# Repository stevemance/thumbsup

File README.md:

# ThumbsUp - Antweight Combat Robot Control System

A complete control system for a 1lb (454g) combat robot using Raspberry Pi Pico W and Bluetooth gamepad control.

## Features

- **Bluetooth Control**: Universal gamepad support via Bluepad32 library (Xbox, PlayStation, Switch Pro, etc.)
- **Differential Drive**: Tank-style mixing with exponential curves for smooth control
- **Weapon Control**: Variable speed brushless weapon with safety arming sequence
- **Safety Systems**: Multiple failsafes including connection loss detection and battery monitoring
- **Status Indicators**: LED feedback for system state, weapon armed, and battery status

## Hardware Components

### Core Electronics
- **Microcontroller**: Raspberry Pi Pico W
- **Power**: 3S LiPo battery (11.1V nominal)

### Motor System
- **Drive Motors**: Repeat Mini Brushed Mk2 (3mm shaft)
- **Drive ESC**: 2-channel brushed motor controller
- **Weapon Motor**: F2822-1100KV brushless outrunner
- **Weapon ESC**: AM32 40A 32-bit ESC

### Control
- **Controller**: Any Bluetooth gamepad supported by Bluepad32
- **Protocol**: Bluetooth Classic (BR/EDR) and BLE support
- **Supported Controllers**: Xbox One/Series, PlayStation 3/4/5, Switch Pro, 8BitDo, and more

## Pin Configuration

| Pin | Function | Description |
|-----|----------|-------------|
| GP0 | PWM Output | Left drive motor signal |
| GP1 | PWM Output | Right drive motor signal |
| GP4 | PWM/DShot Output | Weapon motor signal |
| GP8 | GPIO Input | Safety button (optional, pull-up) |
| GP26 | ADC Input | Battery voltage monitor (ADC0) |
| GP28 | Data Output | SK6812 status LEDs |
| VSYS | Power In | 5V from ESC BEC |
| GND | Ground | Common ground |

See `docs/HARDWARE_SETUP.md` for the full wiring guide.

## Documentation

### 📖 User Manuals
- **[User Manual](docs/USER_MANUAL.md)** - Complete operating instructions, safety procedures, and troubleshooting
- **[Quick Reference](docs/QUICK_REFERENCE.md)** - Single-page quick reference for competition use
- **[Hardware Setup](docs/HARDWARE_SETUP.md)** - Complete pin configuration and wiring guide
- **[HITL (Hardware In The Loop)](docs/HITL.md)** - Fully automated end-to-end tests (robot + emulated controller + host orchestrator)
- **[Building Guide](docs/building.md)** - Compilation and setup instructions
- **[Wiring Guide](docs/wiring_guide.md)** - Hardware connection diagrams

### Control Mapping Summary

| Control | Function |
|---------|----------|
| Left Stick | Drive control (forward/back + turning) |
| Right Stick Y | Weapon speed control (when armed) |
| B Button | Arm/disarm weapon toggle |
| A Button (hold 2s) | Clear emergency stop |
| L1 + R1 | Emergency stop (all motors) |

## Safety Features

### Startup Safety Tests
The robot performs 6 critical safety tests on every startup:

1. **Motor Initialization** - Verifies all motors start in safe positions
2. **Weapon Safety** - Confirms weapon starts disarmed and interlocks work
3. **Failsafe System** - Tests signal loss detection (1.5 second timeout)
4. **Battery Monitoring** - Validates voltage sensing and thresholds
5. **Emergency Stop** - Verifies E-stop functionality
6. **Overflow Protection** - Ensures calculation safety

If any test fails, the robot enters lockout mode with rapid LED flashing and will not operate.

### Runtime Safety Features
- **Connection failsafe** - Motors stop after 1.5s signal loss
- **Low battery protection** - Weapon disabled below 11.1V
- **Emergency stop** - L1+R1 instantly stops all motors
- **Continuous monitoring** - Safety checks run every 10ms
- **Violation counting** - Multiple violations trigger automatic shutdown

## Building the Firmware

### Prerequisites

1. Install the Raspberry Pi Pico SDK:
```bash
git clone https://github.com/raspberrypi/pico-sdk.git
cd pico-sdk
git submodule update --init
export PICO_SDK_PATH=$PWD
```

2. Install Bluepad32:
```bash
git clone https://github.com/ricardoquesada/bluepad32.git
cd bluepad32
git submodule update --init
export BLUEPAD32_ROOT=$PWD
```

3. Install required tools:
```bash
sudo apt update
sudo apt install cmake gcc-arm-none-eabi build-essential
# Install picotool for UF2 generation
cd ~/
git clone https://github.com/raspberrypi/picotool.git
cd picotool
mkdir build && cd build
cmake .. && make
sudo make install
```

### Build Process

#### Quick Build
```bash
export PICO_SDK_PATH=/path/to/pico-sdk
export BLUEPAD32_ROOT=/path/to/bluepad32
cd thumbsup/firmware
mkdir build && cd build
cmake ..
make -j8
```

Output: `firmware/build/thumbsup.uf2`

## Flashing the Firmware

1. Hold the BOOTSEL button on the Pico W
2. Connect the Pico W to your computer via USB
3. Release the BOOTSEL button
4. The Pico will appear as a USB drive
5. Copy `thumbsup.uf2` to the drive
6. The Pico will automatically reboot with the new firmware

## AM32 ESC Configuration

The weapon ESC needs specific configuration for optimal performance:

- Canonical expected AM32 EEPROM config for HITL is tracked at `config/am32/weapon_esc_expected.hexcfg`.
- HITL orchestrator checks/applies this config automatically (write-on-drift) unless `--no-am32-provision` is used.

### Using AM32 Configurator

1. Download AM32 Configurator from [GitHub](https://github.com/AlkaMotors/AM32-MultiRotor-ESC-firmware)
2. Connect the ESC to your computer using a USB-serial adapter
3. Apply these settings:

```
Motor Direction: Forward
Brake on Stop: OFF
Motor Timing: 16 degrees
Startup Power: Medium
PWM Frequency: 24kHz
Temperature Protection: 80°C
Low Voltage Cutoff: Disabled (managed by robot firmware)
Throttle Calibration: 1000-2000μs
Signal Type: Normal PWM
```

## Safety Procedures

### Pre-Competition Checklist

1. **Battery Check**: Ensure battery voltage > 10V
2. **Connection Test**: Verify gamepad connects automatically
3. **Failsafe Test**: Turn off controller, verify motors stop
4. **Weapon Arm**: Test arm sequence (X+Y hold)
5. **Emergency Stop**: Test L1+R1 disarm

### Operating Procedures

1. Power on robot with weapon ESC disconnected
2. Verify drive functions correctly
3. Connect weapon ESC
4. Arm weapon only when in combat arena
5. Always disarm before handling robot

## Wiring Diagram

### Power Distribution
```
3S LiPo Battery
    |
    +-- Drive ESC Power
    |     |
    |     +-- 5V BEC --> Pico VSYS
    |
    +-- Weapon ESC Power
          |
          +-- 1000μF Capacitor (parallel)
```

### Signal Connections
```
Pico GP2 --> Drive ESC CH1 Signal
Pico GP3 --> Drive ESC CH2 Signal
Pico GP4 --> Weapon ESC Signal
All ESC Grounds --> Pico GND
```

### Battery Monitor
```
Battery + --[10kΩ]--+--[3.3kΩ]-- GND
                    |
                 Pico GP26
```

## Troubleshooting

### Bluetooth Connection Issues
- Ensure controller is in pairing mode (varies by controller type)
- Check STATUS LED for connection state
- Reset Pico if connection fails after 10 seconds
- Bluepad32 automatically handles pairing for supported controllers
- For first-time pairing, controller may need to be in discovery mode

### Motor Not Responding
- Verify PWM signal with oscilloscope/logic analyzer
- Check ESC power and ground connections
- Ensure ESC is calibrated for 1000-2000μs range

### Weapon Won't Arm
- Check battery voltage (must be > 9.6V)
- Verify arm sequence is held for full duration
- Check ARMED LED for feedback

## Development

### Debug Mode

Debug output is enabled by default. Connect via serial terminal (115200 baud) to see:
- Bluepad32 controller detection and pairing status
- Gamepad input values
- System state changes

To disable debug output, remove `DEBUG_MODE=1` from the source files.

### Modifying Parameters

Edit `firmware/include/config.h` to adjust:
- Control deadzones
- Speed limits
- Exponential curves
- Timing constants
- Safety thresholds

### Bluetooth Platform Customization

The Bluepad32 platform implementation is in `firmware/src/bluetooth_platform.c`.
Modify the callbacks to customize:
- Controller mapping
- Input processing
- Special button combinations
- Rumble/LED feedback

## CAD Files

Mechanical design files are hosted on Onshape:
[Link to be provided]

## License

This project is open source hardware and software.
- Software: MIT License
- Hardware: CERN-OHL-S v2

## Safety Warning

This is a combat robot with dangerous spinning weapons. Always:
- Wear safety glasses when operating
- Keep weapon pointed away from people
- Use proper arena/test box
- Follow event safety rules
- Have emergency stop ready

## Support

For issues or questions, please open an issue on GitHub.

---

Built with safety and performance in mind for antweight combat robotics.

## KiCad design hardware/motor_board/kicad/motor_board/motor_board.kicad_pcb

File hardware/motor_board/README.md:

# ThumbsUp motor board

Battery in, three brushless channels out, 5 V to the compute board.  Sensorless weapon
(DRV8323RH + 6 FETs), two FOC drive motors with Hall/encoder feedback (2 × DRV8316C), one
STM32G474 running all three, 4S.  Battery input, reverse-polarity protection, pack
monitoring (INA239: V, I, P; BQ76907: per-cell voltages), a soft-start power switch and all
regulation live here.  195 JLC-assembled parts (rev L, after thirty adversarial review rounds in
[review/](review/), then a trim of the speculative firmware policy they had accumulated).

Start with [DESIGN.md](DESIGN.md).  Draw the schematic from [design/nets.md](design/nets.md)
(generated from [design/motor_board.py](design/motor_board.py)); parts in [BOM.md](BOM.md);
MCU pins in [design/mcu_pinmap.md](design/mcu_pinmap.md); SPICE checks in [spice/](spice/);
datasheets in [datasheets/](datasheets/).

```
python3 design/motor_board.py      # re-check the netlist and regenerate nets/BOM/pinmap
python3 design/calcs.py            # regenerate the sizing tables
../tools/.venv/bin/python spice/sim_hotplug.py   # etc., see spice/README.md
```

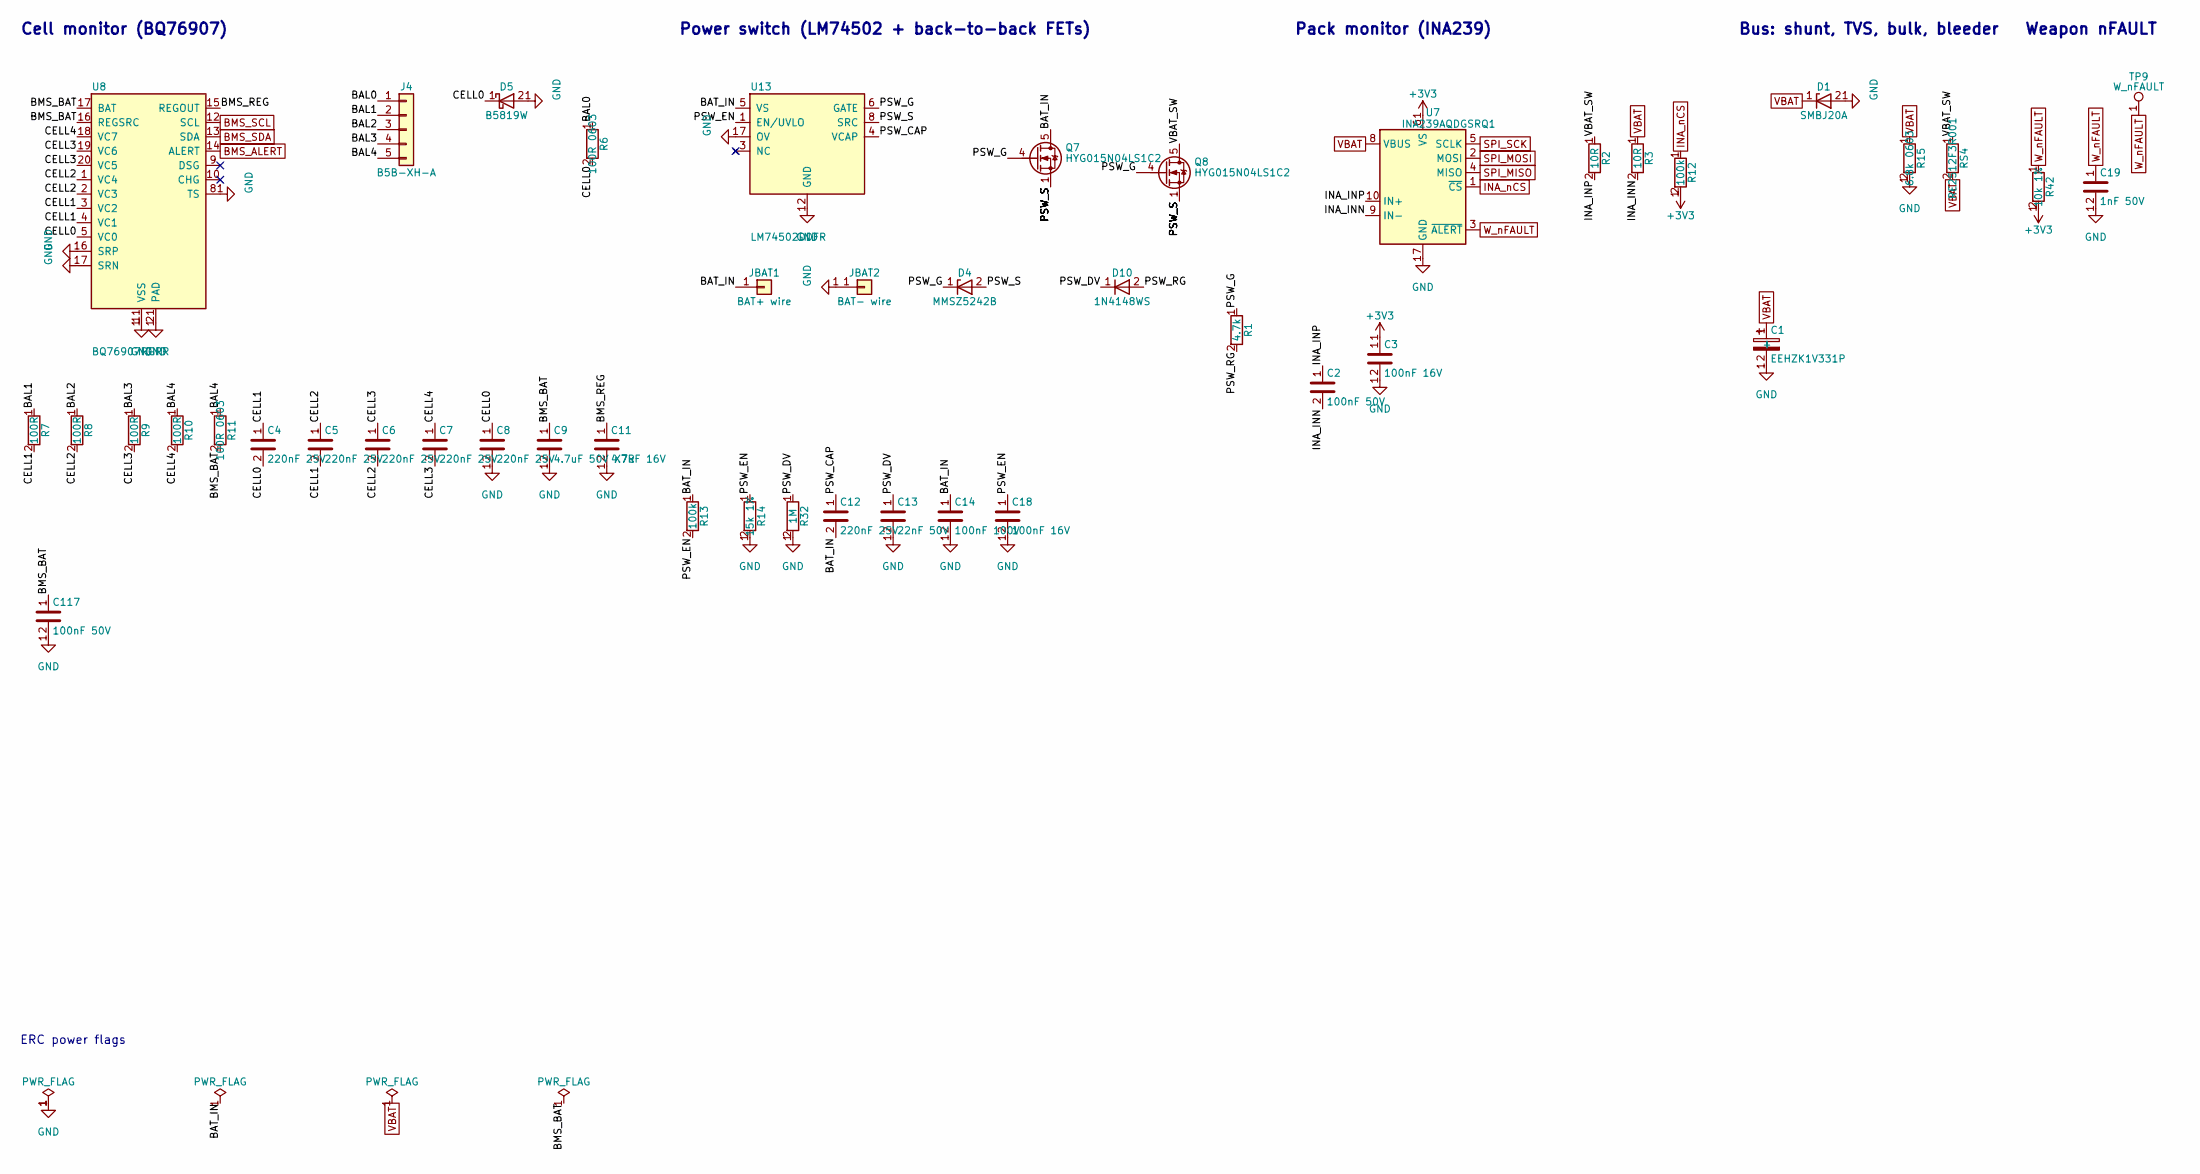
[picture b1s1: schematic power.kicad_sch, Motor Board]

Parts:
C1: EEHZK1V331P; CP_Elec_10x10.5; MPN EEHZK1V331P; LCSC C278516
C2, C117: 100nF 50V; C_0603_1608Metric; LCSC C14663
C3, C18: 100nF 16V; C_0402_1005Metric; LCSC C1525
C4, C5, C6, C7, C8, C12: 220nF 25V; C_0603_1608Metric; LCSC C21120
C9: 4.7uF 50V X7R; C_1206_3216Metric; LCSC C29823
C11: 4.7uF 16V; C_0603_1608Metric; LCSC C19666
C13: 22nF 50V; C_0603_1608Metric; LCSC C21122
C14: 100nF 100V; C_0603_1608Metric; LCSC C15725
C19: 1nF 50V; C_0402_1005Metric; LCSC C1523
D1: SMBJ20A; D_SMB; MPN SMBJ20A; LCSC C151922
D4: MMSZ5242B; D_SOD-123; MPN MMSZ5242B; LCSC C21567
D5: B5819W; D_SOD-123; MPN B5819W; LCSC C8598
D10: 1N4148WS; D_SOD-323; MPN 1N4148WS; LCSC C2128
J4: B5B-XH-A; JST_XH_B5B-XH-A_1x05_P2.50mm_Vertical; MPN B5B-XH-A; LCSC C157991
JBAT1: BAT+ wire; SolderWire-1.5sqmm_1x01_D1.7mm_OD3.9mm
JBAT2: BAT- wire; SolderWire-1.5sqmm_1x01_D1.7mm_OD3.9mm
Q7, Q8: HYG015N04LS1C2; PQFN-8-EP_6x5mm_P1.27mm_Generic; MPN HYG015N04LS1C2; LCSC C2874970
R1: 4.7k; R_0402_1005Metric; LCSC C25900
R2, R3: 10R; R_0402_1005Metric; LCSC C25077
R6, R11: 100R 0603; R_0603_1608Metric; LCSC C22775
R7, R8, R9, R10: 100R; R_0402_1005Metric; LCSC C25076
R12, R13: 100k; R_0402_1005Metric; LCSC C25741
R14: 15k 1%; R_0402_1005Metric; LCSC C25756
R15: 6.8k 0603; R_0603_1608Metric; LCSC C23212
R32: 1M; R_0402_1005Metric; LCSC C26083
R42: 10k 1%; R_0402_1005Metric; LCSC C25744
RS4: RE2512F3R001; R_2512_JIERR_RE_small_electrode; MPN RE2512F3R001; LCSC C46961745
TP9: W_nFAULT; TestPoint_Pad_D1.0mm
U7: INA239AQDGSRQ1; MSOP-10_3x3mm_P0.5mm; MPN INA239AQDGSRQ1; LCSC C4367136
U8: BQ76907RGRR; QFN-20-1EP_3.5x3.5mm_P0.5mm_EP2x2mm; MPN BQ76907RGRR; LCSC C22458649
U13: LM74502DDFR; Texas_DDF0008A_SOT-8_1.6x2.9mm_P0.65mm; MPN LM74502DDFR; LCSC C3236215

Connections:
+3V3: C3.1, R12.2, R42.2, U7.6 (VS); also elsewhere on the board
/power/BAL0: J4.1, R6.1
/power/BAL1: J4.2, R7.1
/power/BAL2: J4.3, R8.1
/power/BAL3: J4.4, R9.1
/power/BAL4: J4.5, R10.1, R11.1
/power/BAT_IN: C12.2, C14.1, JBAT1.1, Q7.5 (D), R13.1, U13.5 (VS)
/power/BMS_BAT: C9.1, C117.1, R11.2, U8.16 (REGSRC), U8.17 (BAT)
/power/BMS_REG: C11.1, U8.15 (REGOUT)
/power/CELL0: C4.2, C8.1, D5.1 (K), R6.2, U8.5 (VC0)
/power/CELL1: C4.1, C5.2, R7.2, U8.3 (VC2), U8.4 (VC1)
/power/CELL2: C5.1, C6.2, R8.2, U8.1 (VC4), U8.2 (VC3)
/power/CELL3: C6.1, C7.2, R9.2, U8.19 (VC6), U8.20 (VC5)
/power/CELL4: C7.1, R10.2, U8.18 (VC7)
/power/INA_INN: C2.2, R3.2, U7.9 (IN-)
/power/INA_INP: C2.1, R2.2, U7.10 (IN+)
/power/PSW_CAP: C12.1, U13.4 (VCAP)
/power/PSW_DV: C13.1, D10.1 (K), R32.1
/power/PSW_EN: C18.1, R13.2, R14.1, U13.1 (EN/UVLO)
/power/PSW_G: D4.1 (K), Q7.4 (G), Q8.4 (G), R1.1, U13.6 (GATE)
/power/PSW_RG: D10.2 (A), R1.2
/power/PSW_S: D4.2 (A), Q7.1 (S), Q7.2 (S), Q7.3 (S), Q8.1 (S), Q8.2 (S), Q8.3 (S), U13.8 (SRC)
/power/VBAT_SW: Q8.5 (D), R2.1, RS4.1
BMS_ALERT: U8.14 (ALERT); also elsewhere on the board
BMS_SCL: U8.12 (SCL); also elsewhere on the board
BMS_SDA: U8.13 (SDA); also elsewhere on the board
GND: C1.2 (-), C3.2, C8.2, C9.2, C11.2, C13.2, C14.2, C18.2, C19.2, C117.2, D1.2 (A), D5.2 (A), JBAT2.1, R14.2, R15.2, R32.2, U7.7 (GND), U8.6 (SRP), U8.7 (SRN), U8.8 (TS), U8.11 (VSS), U8.21 (PAD), U13.2 (GND), U13.7 (OV); also elsewhere on the board
INA_nCS: R12.1, U7.1 (~CS); also elsewhere on the board
SPI_MISO: U7.4 (MISO); also elsewhere on the board
SPI_MOSI: U7.2 (MOSI); also elsewhere on the board
SPI_SCK: U7.5 (SCLK); also elsewhere on the board
VBAT: C1.1 (+), D1.1 (K), R3.1, R15.1, RS4.2, U7.8 (VBUS); also elsewhere on the board
W_nFAULT: C19.1, R42.1, TP9.1, U7.3 (~ALERT); also elsewhere on the board

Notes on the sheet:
ERC power flags
Cell monitor (BQ76907)
Power switch (LM74502 + back-to-back FETs)
Pack monitor (INA239)
Bus: shunt, TVS, bulk, bleeder
Weapon nFAULT

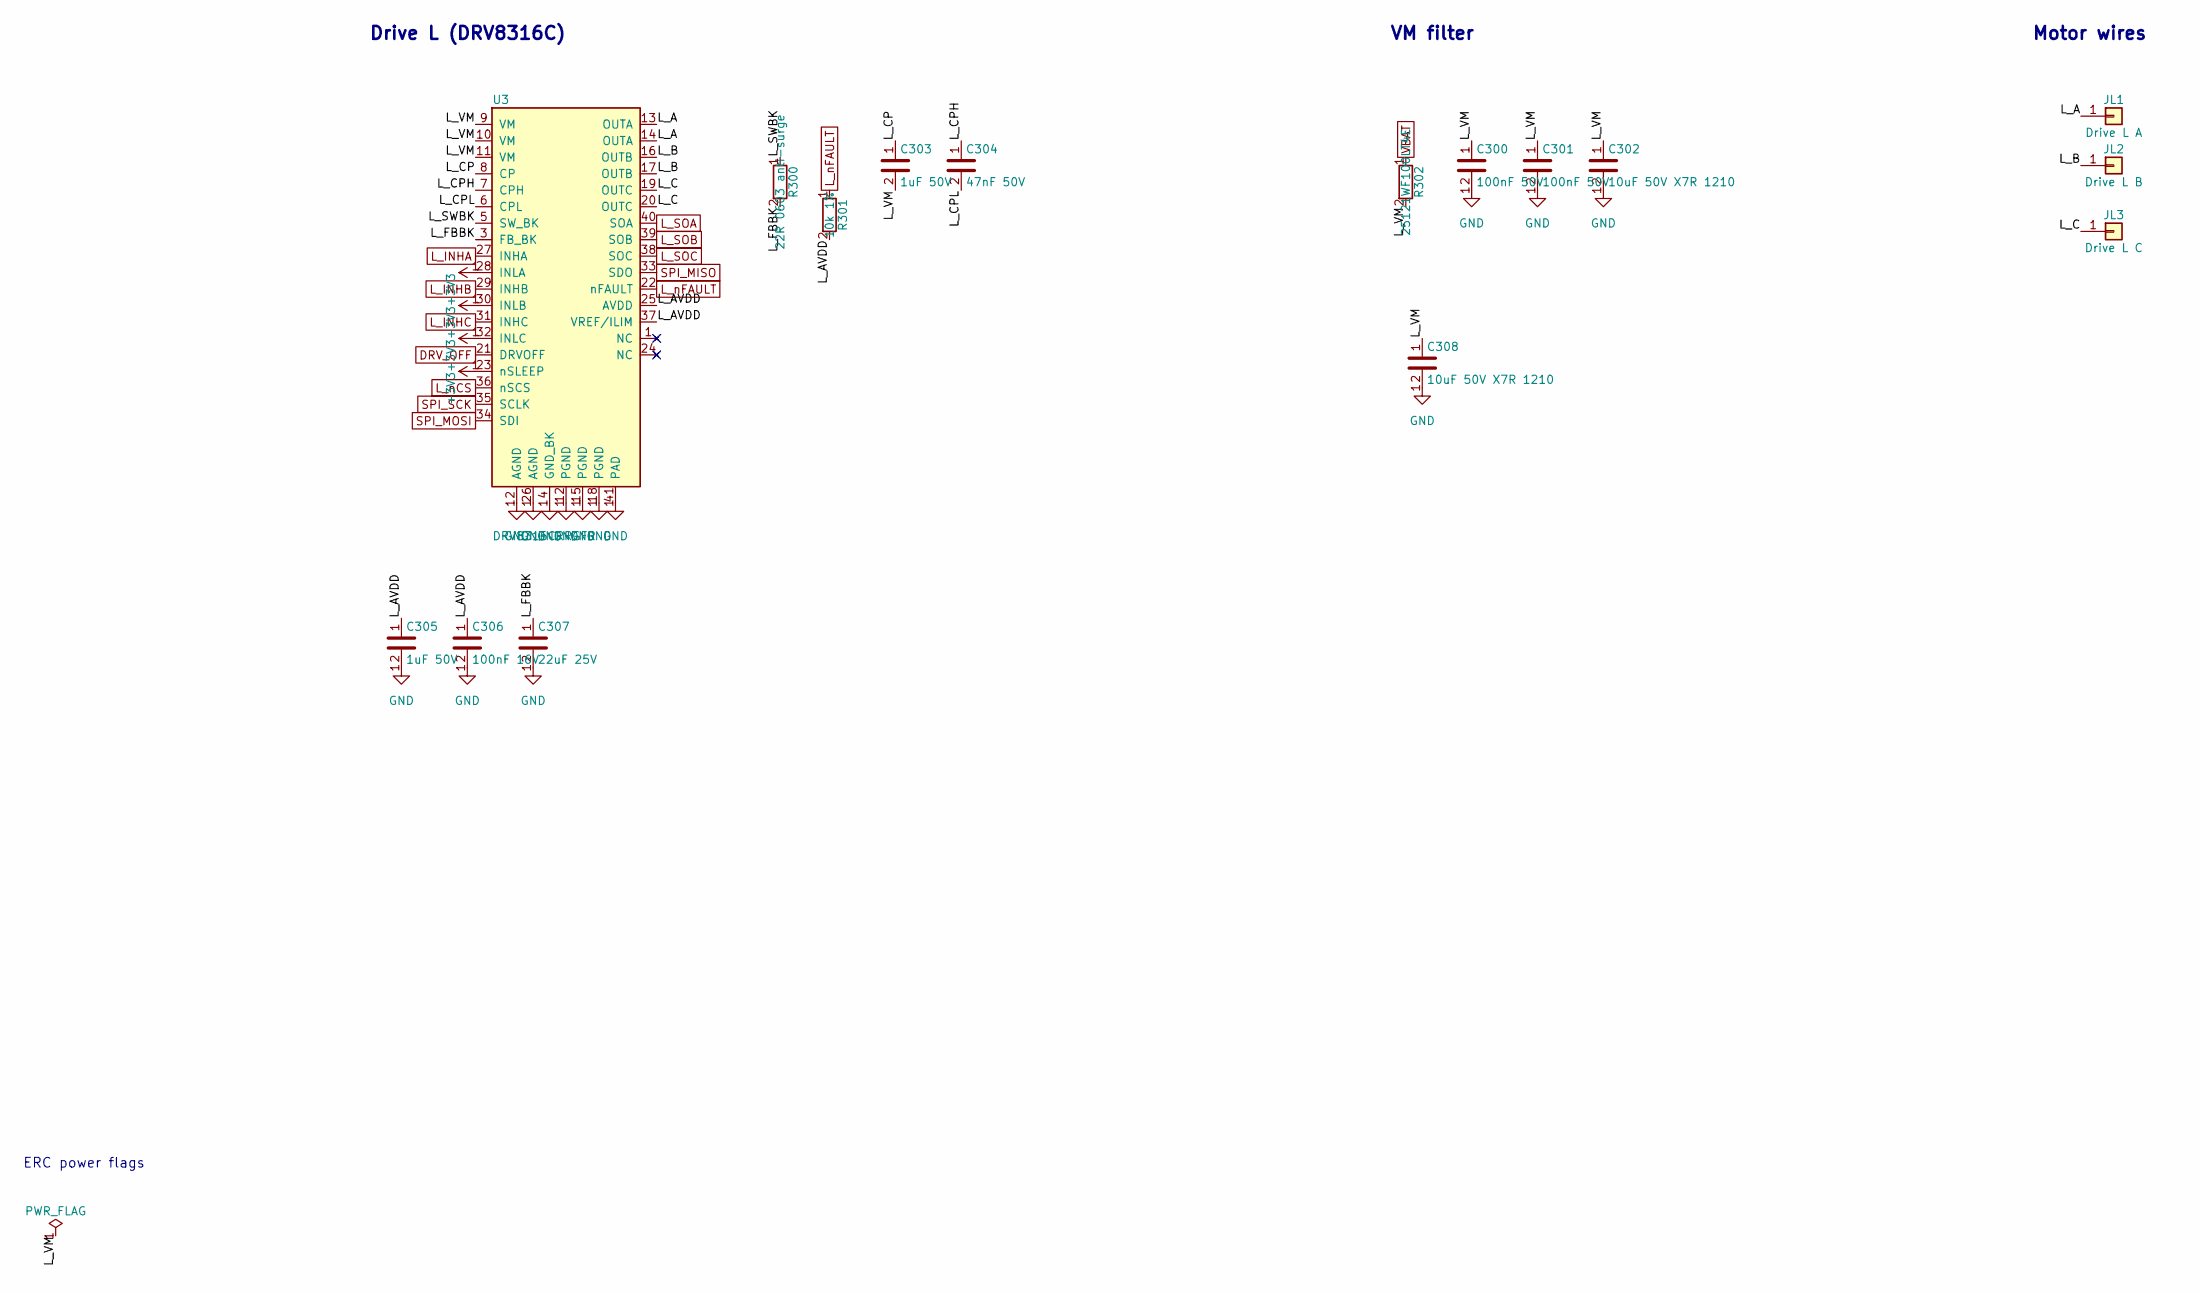
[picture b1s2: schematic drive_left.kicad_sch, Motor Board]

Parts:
C300, C301: 100nF 50V; C_0603_1608Metric; LCSC C14663
C302, C308: 10uF 50V X7R 1210; C_1210_3225Metric; LCSC C77102
C303, C305: 1uF 50V; C_0603_1608Metric; LCSC C15849
C304: 47nF 50V; C_0603_1608Metric; LCSC C1622
C306: 100nF 16V; C_0402_1005Metric; LCSC C1525
C307: 22uF 25V; C_0805_2012Metric; LCSC C45783
JL1: Drive L A; SolderWire-0.5sqmm_1x01_D0.9mm_OD2.1mm
JL2: Drive L B; SolderWire-0.5sqmm_1x01_D0.9mm_OD2.1mm
JL3: Drive L C; SolderWire-0.5sqmm_1x01_D0.9mm_OD2.1mm
R300: 22R 0603 anti-surge; R_0603_1608Metric; LCSC C2074038
R301: 10k 1%; R_0402_1005Metric; LCSC C25744
R302: 25121WF100LT4E; R_2512_6332Metric; MPN 25121WF100LT4E; LCSC C25466
U3: DRV8316CRRGFR; TI_RGF0040E_VQFN-40-1EP_5x7mm_P0.5mm_EP3.7x5.7mm; MPN DRV8316CRRGFR; LCSC C5447274

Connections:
+3V3: U3.23 (nSLEEP), U3.28 (INLA), U3.30 (INLB), U3.32 (INLC); also elsewhere on the board
/drive_left/L_A: JL1.1, U3.13 (OUTA), U3.14 (OUTA)
/drive_left/L_AVDD: C305.1, C306.1, R301.2, U3.25 (AVDD), U3.37 (VREF/ILIM)
/drive_left/L_B: JL2.1, U3.16 (OUTB), U3.17 (OUTB)
/drive_left/L_C: JL3.1, U3.19 (OUTC), U3.20 (OUTC)
/drive_left/L_CP: C303.1, U3.8 (CP)
/drive_left/L_CPH: C304.1, U3.7 (CPH)
/drive_left/L_CPL: C304.2, U3.6 (CPL)
/drive_left/L_FBBK: C307.1, R300.2, U3.3 (FB_BK)
/drive_left/L_SWBK: R300.1, U3.5 (SW_BK)
/drive_left/L_VM: C300.1, C301.1, C302.1, C303.2, C308.1, R302.2, U3.9 (VM), U3.10 (VM), U3.11 (VM)
DRV_OFF: U3.21 (DRVOFF); also elsewhere on the board
GND: C300.2, C301.2, C302.2, C305.2, C306.2, C307.2, C308.2, U3.2 (AGND), U3.4 (GND_BK), U3.12 (PGND), U3.15 (PGND), U3.18 (PGND), U3.26 (AGND), U3.41 (PAD); also elsewhere on the board
L_INHA: U3.27 (INHA); also elsewhere on the board
L_INHB: U3.29 (INHB); also elsewhere on the board
L_INHC: U3.31 (INHC); also elsewhere on the board
L_SOA: U3.40 (SOA); also elsewhere on the board
L_SOB: U3.39 (SOB); also elsewhere on the board
L_SOC: U3.38 (SOC); also elsewhere on the board
L_nCS: U3.36 (nSCS); also elsewhere on the board
L_nFAULT: R301.1, U3.22 (nFAULT); also elsewhere on the board
SPI_MISO: U3.33 (SDO); also elsewhere on the board
SPI_MOSI: U3.34 (SDI); also elsewhere on the board
SPI_SCK: U3.35 (SCLK); also elsewhere on the board
VBAT: R302.1; also elsewhere on the board

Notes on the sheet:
ERC power flags
Drive L (DRV8316C)
VM filter
Motor wires

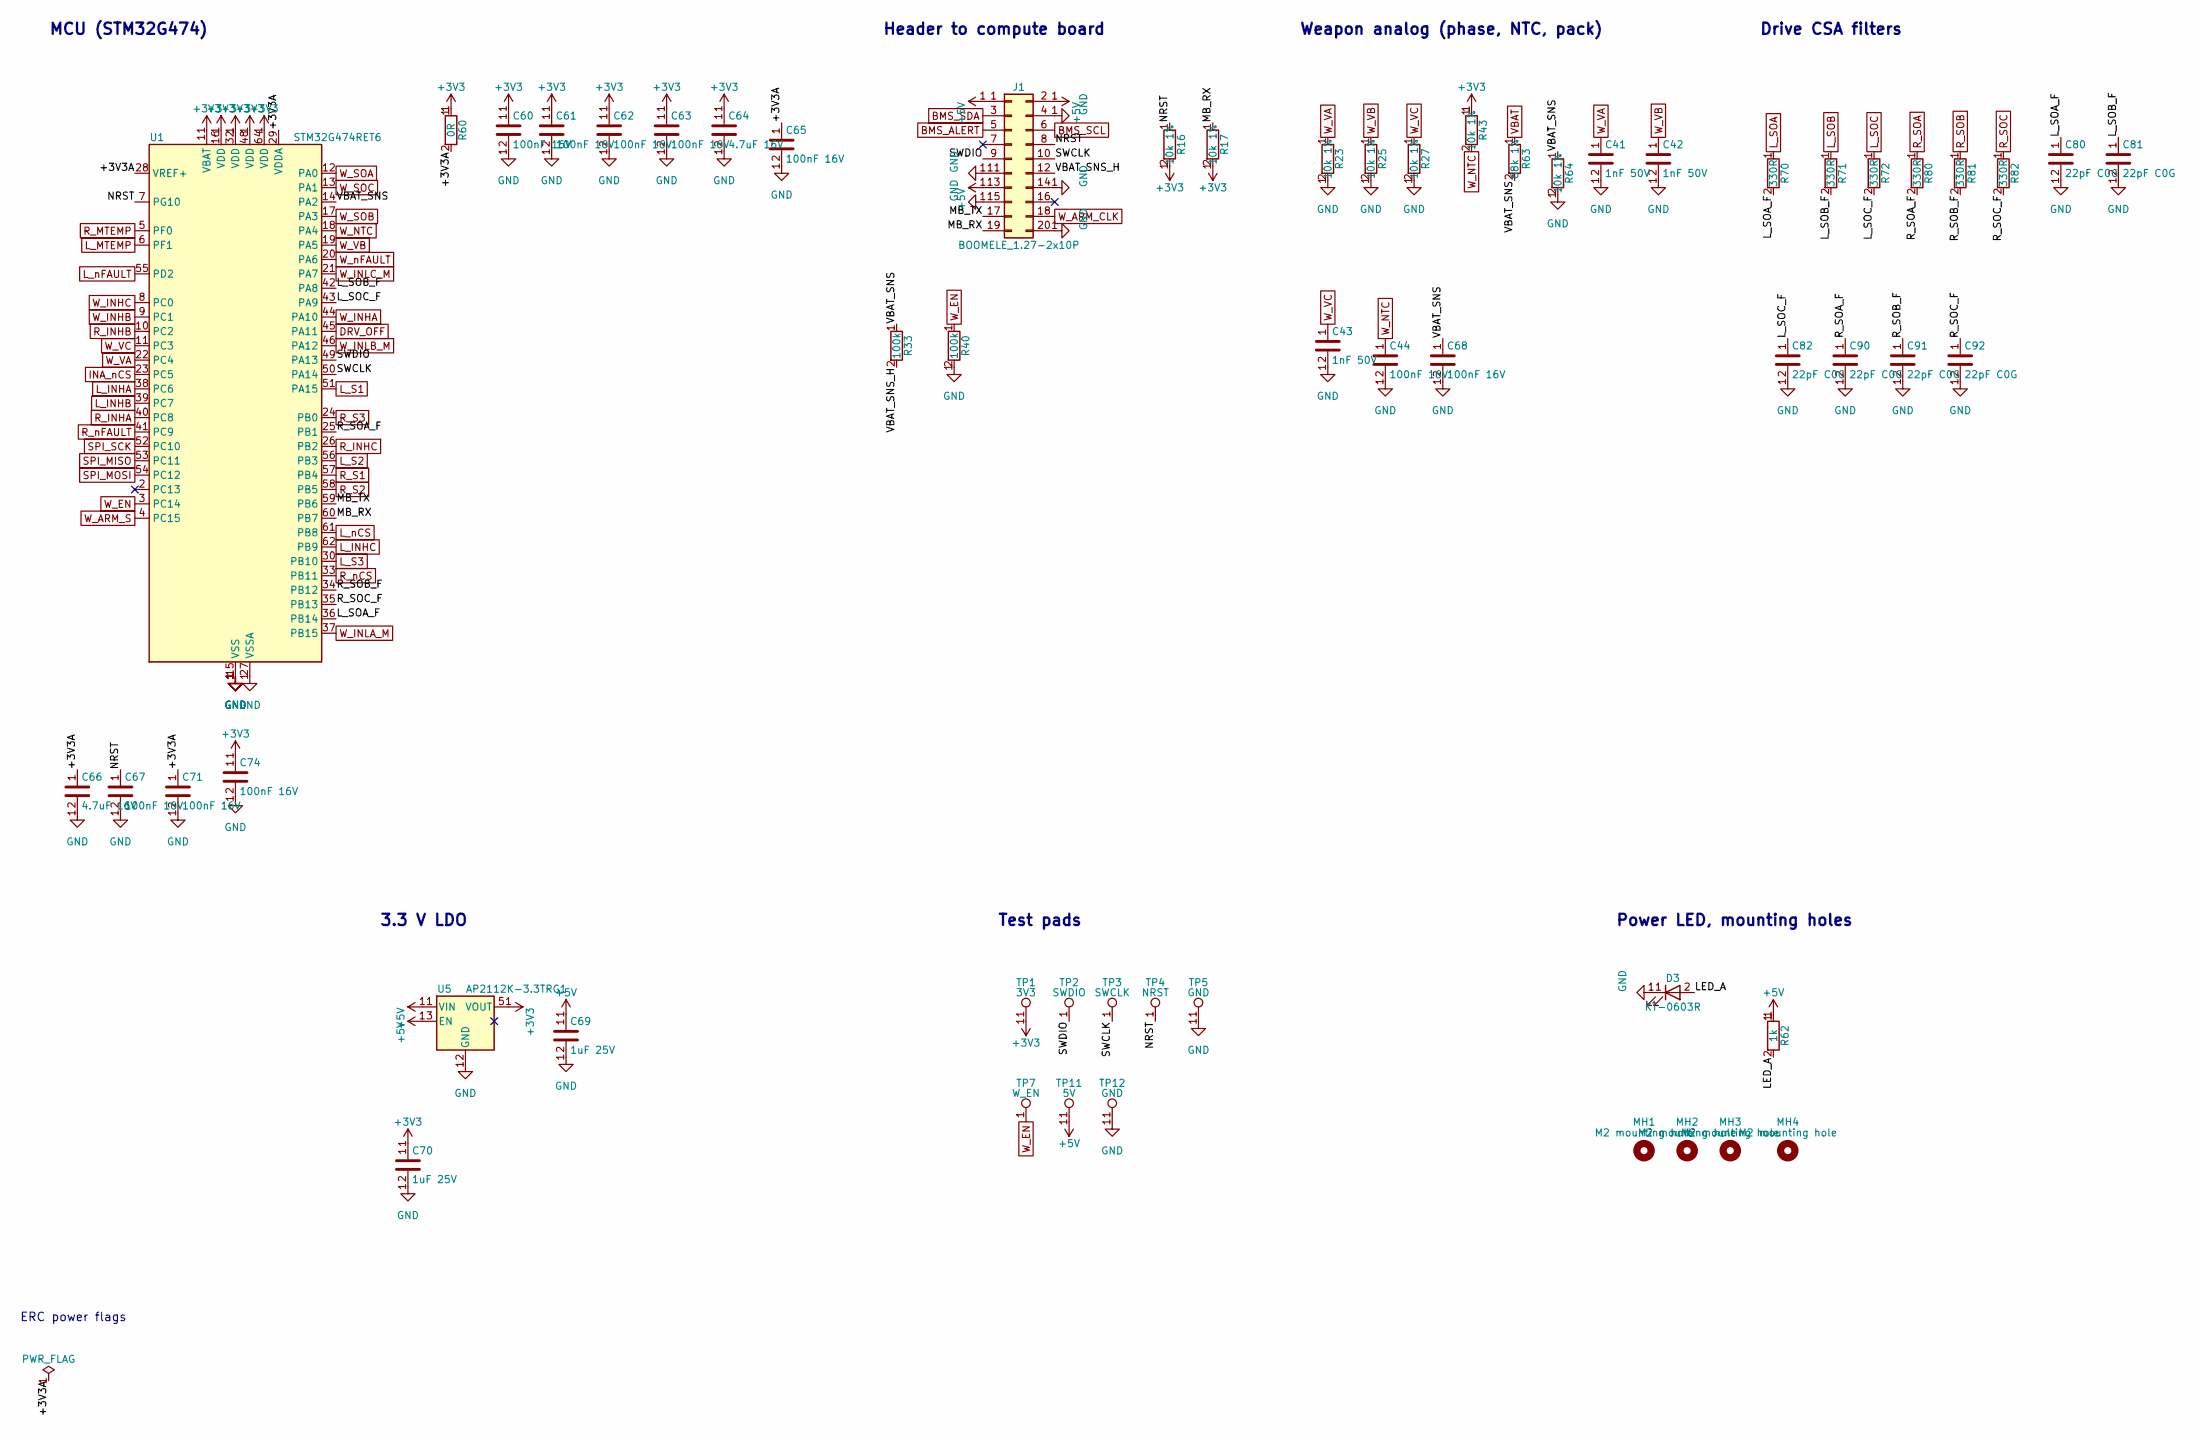
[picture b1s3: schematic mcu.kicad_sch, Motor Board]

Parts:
C41, C42, C43: 1nF 50V; C_0402_1005Metric; LCSC C1523
C44, C60, C61, C62, C63, C65, C67, C68, C71, C74: 100nF 16V; C_0402_1005Metric; LCSC C1525
C64, C66: 4.7uF 16V; C_0603_1608Metric; LCSC C19666
C69, C70: 1uF 25V; C_0402_1005Metric; LCSC C52923
C80, C81, C82, C90, C91, C92: 22pF C0G; C_0402_1005Metric; LCSC C1555
D3: KT-0603R; LED_0603_1608Metric; MPN KT-0603R; LCSC C2286
J1: BOOMELE_1.27-2x10P; BOOMELE_1.27-2x10P_SMD; MPN BOOMELE_1.27-2x10P; LCSC C59981
MH1, MH2, MH3, MH4: M2 mounting hole; MountingHole_2.2mm_M2
R16, R17, R23, R25, R27, R43, R64: 10k 1%; R_0402_1005Metric; LCSC C25744
R33, R40: 100k; R_0402_1005Metric; LCSC C25741
R60: 0R; R_0402_1005Metric; LCSC C17168
R62: 1k; R_0402_1005Metric; LCSC C11702
R63: 68k 1%; R_0402_1005Metric; LCSC C36871
R70, R71, R72, R80, R81, R82: 330R; R_0402_1005Metric; LCSC C25104
TP1: 3V3; TestPoint_Pad_D1.0mm
TP2: SWDIO; TestPoint_Pad_D1.0mm
TP3: SWCLK; TestPoint_Pad_D1.0mm
TP4: NRST; TestPoint_Pad_D1.0mm
TP5, TP12: GND; TestPoint_Pad_D1.0mm
TP7: W_EN; TestPoint_Pad_D1.0mm
TP11: 5V; TestPoint_Pad_D1.0mm
U1: STM32G474RET6; LQFP-64_10x10mm_P0.5mm; MPN STM32G474RET6; LCSC C521608
U5: AP2112K-3.3TRG1; SOT-23-5; MPN AP2112K-3.3TRG1; LCSC C51118

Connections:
+3V3: C60.1, C61.1, C62.1, C63.1, C64.1, C70.1, C74.1, R16.2, R17.2, R43.1, R60.1, TP1.1, U1.1 (VBAT), U1.16 (VDD), U1.32 (VDD), U1.48 (VDD), U1.64 (VDD), U5.5 (VOUT); also elsewhere on the board
+5V: C69.1, J1.1, J1.2, J1.13, R62.1, TP11.1, U5.1 (VIN), U5.3 (EN); also elsewhere on the board
/mcu/+3V3A: C65.1, C66.1, C71.1, R60.2, U1.28 (VREF+), U1.29 (VDDA)
/mcu/LED_A: D3.2 (A), R62.2
/mcu/L_SOA_F: C80.1, R70.2, U1.36 (PB14)
/mcu/L_SOB_F: C81.1, R71.2, U1.42 (PA8)
/mcu/L_SOC_F: C82.1, R72.2, U1.43 (PA9)
/mcu/MB_RX: J1.19, R17.1, U1.60 (PB7)
/mcu/MB_TX: J1.17, U1.59 (PB6)
/mcu/NRST: C67.1, J1.8, R16.1, TP4.1, U1.7 (PG10)
/mcu/R_SOA_F: C90.1, R80.2, U1.25 (PB1)
/mcu/R_SOB_F: C91.1, R81.2, U1.34 (PB12)
/mcu/R_SOC_F: C92.1, R82.2, U1.35 (PB13)
/mcu/SWCLK: J1.10, TP3.1, U1.50 (PA14)
/mcu/SWDIO: J1.9, TP2.1, U1.49 (PA13)
/mcu/VBAT_SNS: C68.1, R33.1, R63.2, R64.1, U1.14 (PA2)
/mcu/VBAT_SNS_H: J1.12, R33.2
BMS_ALERT: J1.5; also elsewhere on the board
BMS_SCL: J1.6; also elsewhere on the board
BMS_SDA: J1.3; also elsewhere on the board
DRV_OFF: U1.45 (PA11); also elsewhere on the board
GND: C41.2, C42.2, C43.2, C44.2, C60.2, C61.2, C62.2, C63.2, C64.2, C65.2, C66.2, C67.2, C68.2, C69.2, C70.2, C71.2, C74.2, C80.2, C81.2, C82.2, C90.2, C91.2, C92.2, D3.1 (K), J1.4, J1.11, J1.14, J1.15, J1.20, R23.2, R25.2, R27.2, R40.2, R64.2, TP5.1, TP12.1, U1.15 (VSS), U1.27 (VSSA), U1.31 (VSS), U1.47 (VSS), U1.63 (VSS), U5.2 (GND); also elsewhere on the board
INA_nCS: U1.23 (PC5); also elsewhere on the board
L_INHA: U1.38 (PC6); also elsewhere on the board
L_INHB: U1.39 (PC7); also elsewhere on the board
L_INHC: U1.62 (PB9); also elsewhere on the board
L_MTEMP: U1.6 (PF1); also elsewhere on the board
L_S1: U1.51 (PA15); also elsewhere on the board
L_S2: U1.56 (PB3); also elsewhere on the board
L_S3: U1.30 (PB10); also elsewhere on the board
L_SOA: R70.1; also elsewhere on the board
L_SOB: R71.1; also elsewhere on the board
L_SOC: R72.1; also elsewhere on the board
L_nCS: U1.61 (PB8); also elsewhere on the board
L_nFAULT: U1.55 (PD2); also elsewhere on the board
R_INHA: U1.40 (PC8); also elsewhere on the board
R_INHB: U1.10 (PC2); also elsewhere on the board
R_INHC: U1.26 (PB2); also elsewhere on the board
R_MTEMP: U1.5 (PF0); also elsewhere on the board
R_S1: U1.57 (PB4); also elsewhere on the board
R_S2: U1.58 (PB5); also elsewhere on the board
R_S3: U1.24 (PB0); also elsewhere on the board
R_SOA: R80.1; also elsewhere on the board
R_SOB: R81.1; also elsewhere on the board
R_SOC: R82.1; also elsewhere on the board
R_nCS: U1.33 (PB11); also elsewhere on the board
R_nFAULT: U1.41 (PC9); also elsewhere on the board
SPI_MISO: U1.53 (PC11); also elsewhere on the board
SPI_MOSI: U1.54 (PC12); also elsewhere on the board
SPI_SCK: U1.52 (PC10); also elsewhere on the board
VBAT: R63.1; also elsewhere on the board
W_ARM_CLK: J1.18; also elsewhere on the board
W_ARM_S: U1.4 (PC15); also elsewhere on the board
W_EN: R40.1, TP7.1, U1.3 (PC14); also elsewhere on the board
W_INHA: U1.44 (PA10); also elsewhere on the board
W_INHB: U1.9 (PC1); also elsewhere on the board
W_INHC: U1.8 (PC0); also elsewhere on the board
W_INLA_M: U1.37 (PB15); also elsewhere on the board
W_INLB_M: U1.46 (PA12); also elsewhere on the board
W_INLC_M: U1.21 (PA7); also elsewhere on the board
W_NTC: C44.1, R43.2, U1.18 (PA4); also elsewhere on the board
W_SOA: U1.12 (PA0); also elsewhere on the board
W_SOB: U1.17 (PA3); also elsewhere on the board
W_SOC: U1.13 (PA1); also elsewhere on the board
W_VA: C41.1, R23.1, U1.22 (PC4); also elsewhere on the board
W_VB: C42.1, R25.1, U1.19 (PA5); also elsewhere on the board
W_VC: C43.1, R27.1, U1.11 (PC3); also elsewhere on the board
W_nFAULT: U1.20 (PA6); also elsewhere on the board

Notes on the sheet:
ERC power flags
MCU (STM32G474)
Header to compute board
Weapon analog (phase, NTC, pack)
Drive CSA filters
3.3 V LDO
Test pads
Power LED, mounting holes

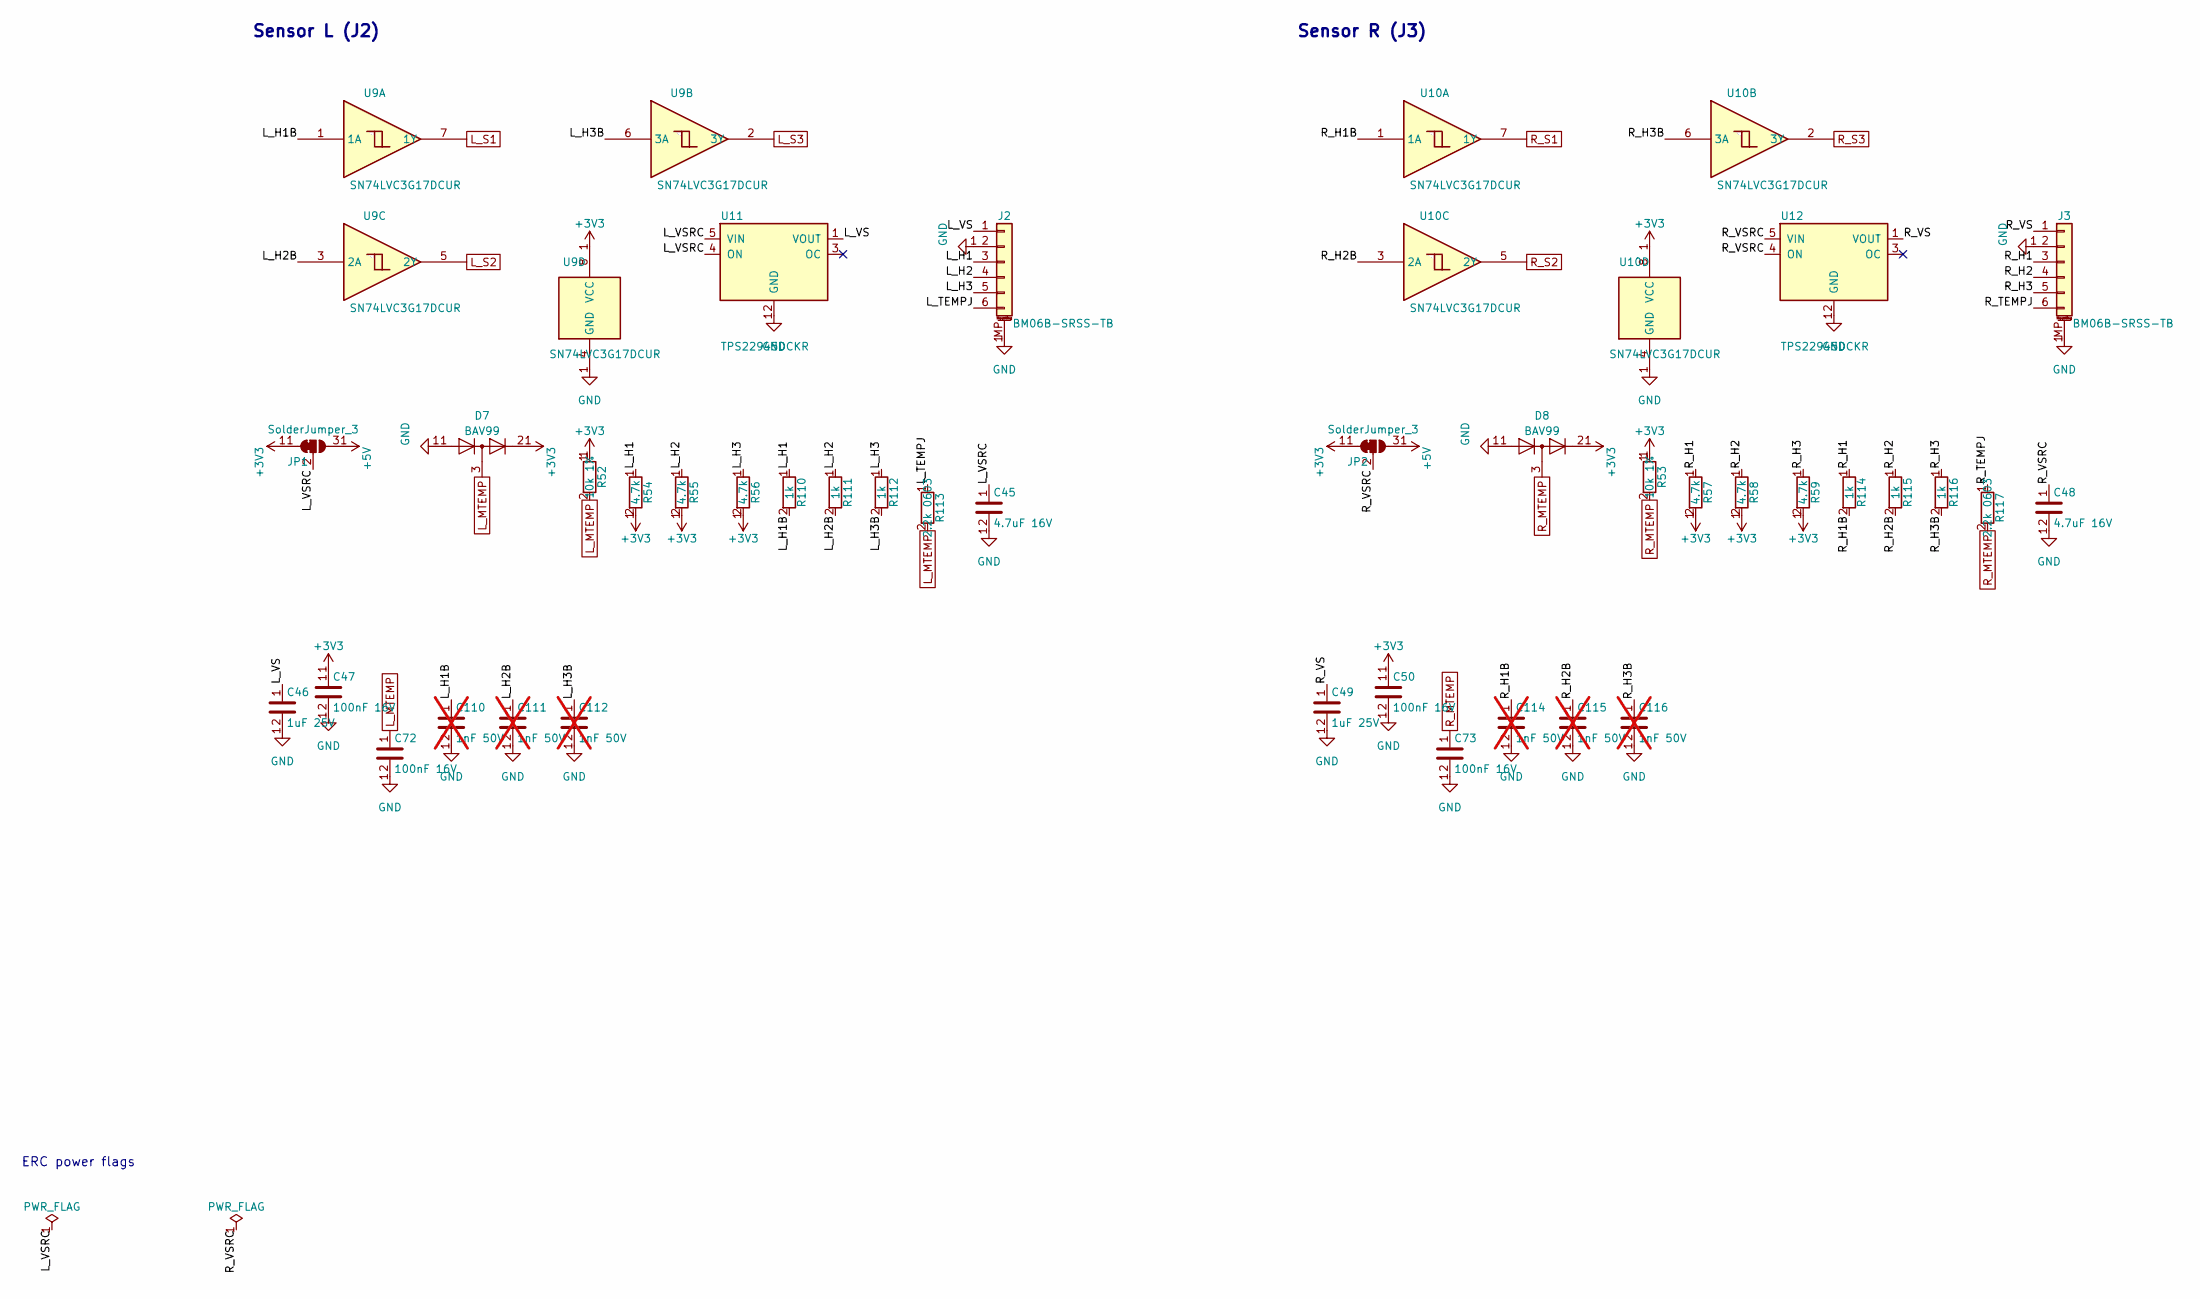
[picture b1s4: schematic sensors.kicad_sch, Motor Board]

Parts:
C45, C48: 4.7uF 16V; C_0603_1608Metric; LCSC C19666
C46, C49: 1uF 25V; C_0402_1005Metric; LCSC C52923
C47, C50, C72, C73: 100nF 16V; C_0402_1005Metric; LCSC C1525
C110, C111, C112, C114, C115, C116: 1nF 50V; C_0402_1005Metric; LCSC C1523; not fitted
D7, D8: BAV99; SOT-23; MPN BAV99; LCSC C2500
J2, J3: BM06B-SRSS-TB; JST_SH_BM06B-SRSS-TB_1x06-1MP_P1.00mm_Vertical; MPN BM06B-SRSS-TB; LCSC C160392
JP1, JP2: SolderJumper_3; SolderJumper-3_P1.3mm_Bridged12_RoundedPad1.0x1.5mm
R52, R53: 10k 1%; R_0402_1005Metric; LCSC C25744
R54, R55, R56, R57, R58, R59: 4.7k; R_0402_1005Metric; LCSC C25900
R110, R111, R112, R114, R115, R116: 1k; R_0402_1005Metric; LCSC C11702
R113, R117: 2.2k 0603; R_0603_1608Metric; LCSC C4190
U9, U10: SN74LVC3G17DCUR; VSSOP-8_2.3x2mm_P0.5mm; MPN SN74LVC3G17DCUR; LCSC C68245
U11, U12: TPS22945DCKR; SOT-353_SC-70-5; MPN TPS22945DCKR; LCSC C47507

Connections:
+3V3: C47.1, C50.1, D7.2 (K2), D8.2 (K2), JP1.1 (A), JP2.1 (A), R52.1, R53.1, R54.2, R55.2, R56.2, R57.2, R58.2, R59.2, U9.8 (VCC), U10.8 (VCC); also elsewhere on the board
+5V: JP1.3 (B), JP2.3 (B); also elsewhere on the board
/sensors/L_H1: J2.3, R54.1, R110.1
/sensors/L_H1B: C110.1, R110.2, U9.1 (1A)
/sensors/L_H2: J2.4, R55.1, R111.1
/sensors/L_H2B: C111.1, R111.2, U9.3 (2A)
/sensors/L_H3: J2.5, R56.1, R112.1
/sensors/L_H3B: C112.1, R112.2, U9.6 (3A)
/sensors/L_TEMPJ: J2.6, R113.1
/sensors/L_VS: C46.1, J2.1, U11.1 (VOUT)
/sensors/L_VSRC: C45.1, JP1.2 (C), U11.4 (ON), U11.5 (VIN)
/sensors/R_H1: J3.3, R57.1, R114.1
/sensors/R_H1B: C114.1, R114.2, U10.1 (1A)
/sensors/R_H2: J3.4, R58.1, R115.1
/sensors/R_H2B: C115.1, R115.2, U10.3 (2A)
/sensors/R_H3: J3.5, R59.1, R116.1
/sensors/R_H3B: C116.1, R116.2, U10.6 (3A)
/sensors/R_TEMPJ: J3.6, R117.1
/sensors/R_VS: C49.1, J3.1, U12.1 (VOUT)
/sensors/R_VSRC: C48.1, JP2.2 (C), U12.4 (ON), U12.5 (VIN)
GND: C45.2, C46.2, C47.2, C48.2, C49.2, C50.2, C72.2, C73.2, C110.2, C111.2, C112.2, C114.2, C115.2, C116.2, D7.1 (A1), D8.1 (A1), J2.2, J2.MP (MountPin), J3.2, J3.MP (MountPin), U9.4 (GND), U10.4 (GND), U11.2 (GND), U12.2 (GND); also elsewhere on the board
L_MTEMP: C72.1, D7.3 (K1A2), R52.2, R113.2; also elsewhere on the board
L_S1: U9.7 (1Y); also elsewhere on the board
L_S2: U9.5 (2Y); also elsewhere on the board
L_S3: U9.2 (3Y); also elsewhere on the board
R_MTEMP: C73.1, D8.3 (K1A2), R53.2, R117.2; also elsewhere on the board
R_S1: U10.7 (1Y); also elsewhere on the board
R_S2: U10.5 (2Y); also elsewhere on the board
R_S3: U10.2 (3Y); also elsewhere on the board

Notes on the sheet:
ERC power flags
Sensor L (J2)
Sensor R (J3)
